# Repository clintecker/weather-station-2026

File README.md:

# Weather Station: bench prototype software

A home weather station, still on the bench. A sensor node (an STM32WL NUCLEO board) samples its sensors every 15 seconds. Once a minute it sends one observation, a summary of that minute, over encrypted LoRa to a second board on USB. A Python gateway (`ws0`) stores each reading in SQLite and acknowledges it over the radio. The gateway then serves the reading over a local HTTP API, a web dashboard and optional MQTT for Home Assistant.

This repository holds the firmware, the gateway, the tests, a fault-injection simulator, the bench hardware files and the dated evidence of each bench run.

Authority: the **Weather Station v0.2 product and technical requirements document (PRD/TRD), 8 October 2026**, sections 3, 9, 11 and the 24-hour delivery test (H01). H01 lives in section 12 of that document. The PRD/TRD itself is not in this repository.

Where things stand:

- The Python gateway (`ws0`) and the firmware for two NUCLEO-WL55JC1 boards (`firmware/stage0-node/`) live here.
- The boards run release `04fcc656938d` (TX) and `cc2766a38c61` (RX), protocol version 5. We built, flashed and tested that release on the bench, with the gateway of that release.
- Master is a step ahead. The firmware and the gateway on master speak protocol version 6 (power telemetry). Nobody cut them as a release yet, and they never met the boards ([`firmware/stage0-node/RELEASES.md`](firmware/stage0-node/RELEASES.md), "Next release").
- The project is the breadboarded development version (build steps 1 and 1b). We removed the later stages from the repository on 2026-11-02. Git history still has them.
- **The 24-hour delivery test (H01, [`docs/H01-checklist.md`](docs/H01-checklist.md)) did NOT RUN yet.**

Back at the bench after a break? Start with [`docs/CONTEXT-PACK.md`](docs/CONTEXT-PACK.md). Other entry points:

- Firmware: [`firmware/stage0-node/README.md`](firmware/stage0-node/README.md).
- Releases: [`firmware/stage0-node/RELEASES.md`](firmware/stage0-node/RELEASES.md).
- Move boards between gateways: [`docs/runbook-moving-boards.md`](docs/runbook-moving-boards.md).
- Tools: [`tools/README.md`](tools/README.md).
- The build sheets: [The bench build sheets](#the-bench-build-sheets).
- Every other document and package: [Where things are](#where-things-are).

The data path with the boards:

```mermaid
flowchart LR
  S["Sensor modules<br/>SHT45 and the bench station"] -->|"I2C, GPIO, ADC"| TX["TX board<br/>sensor node"]
  TX -->|"LoRa: encrypted observation"| RX["RX board<br/>USB bridge"]
  RX -->|"USB serial: hex line"| GW["Gateway<br/>ws0 serve"]
  GW --> DB[("SQLite")]
  GW -->|"ACK after the commit"| RX
  RX -->|"LoRa: encrypted ACK"| TX
  GW --> API["HTTP API<br/>127.0.0.1:8088"]
  GW -->|"optional"| MQ["MQTT broker"]
  MQ --> HA["Home Assistant"]
  API --> ST["tools/status.py"]
```

In the simulated demo, `ws0 demo` stands in for the boards. It sends encrypted frames to the same gateway code.

## The bench build sheets

The bench build sheets are illustrated PDFs that walk you through building the hardware, one step per page. They're the nicest thing in here, so have a look.

There are two sets:

- **TX stack, Sessions 1 to 5** (`hardware/tx-stack-r1/sheets/`). The printed base, the backplane and the four cards (B1 to B4) in their keyed 1x30 sockets.
- **Pods, Sessions P and Q** (`hardware/pods-r1/sheets/`). Session P builds the three pod boards and the port cable. Session Q covers the boxes, the shield and the install.

Why they are good:

- **Real geometry.** Every illustration comes from 3D models of the real parts (CadQuery and OpenCascade), with hidden lines removed and flat colour on each face. The renderer refuses a mirrored picture of a real object.
- **Exact parts.** The labels name the board, the face, the hole and the lead: "B4 POWER, TOP FACE", "X1 VIN+ (LEAD L2)", "backplane holes 13, 19, 27, 35". Nobody has to guess what "the card" means.
- **One step per page.** Each page opens with one big step number in a hazard-yellow box, then numbered panels with short captions.
- **Label chips that never collide.** Each label sits on a paper chip, and its leader stops at the chip edge. The build checks every page for chips that overlap, cross a panel edge or sit under another leader. One bad chip, and the build stops with `BUILD FAILED: label or hole-callout issues`.

The full tour, how the pipeline works and a reusable skill for other projects are in [`docs/build-sheets/README.md`](docs/build-sheets/README.md) and [`docs/build-sheets/skill/SKILL.md`](docs/build-sheets/skill/SKILL.md). The PDFs build into each `sheets/out/` folder and stay out of git.

## Run the simulated demo on your Mac

You don't need any boards for this. The demo fakes the radio side and runs the real gateway. Python 3.12 is the tested baseline. Open this folder in VS Code and run:

```sh
python3 -m venv .venv
source .venv/bin/activate
python -m pip install -r requirements.txt
python -m ws0 init
python -m ws0 demo
```

`init` creates a private `run-demo` directory with a fresh radio key, an API token and persistent nonce state. It refuses to overwrite an existing directory.

`demo` sends one simulated sample at once, then one every 60 seconds. It tests the path from encrypted frame to gateway to SQLite to encrypted ACK. The station name in records, the API and the MQTT topics is `simulation-01`. Its numeric radio station ID is 1. Ctrl-C stops the demo. Run `demo` again, and it resumes with a new observation epoch and the old queued history.

In a second terminal, from the same folder:

```sh
source .venv/bin/activate
python tools/status.py
```

This shows the live status and does not print your API token. The read-only API listens at `127.0.0.1:8088`. Every request needs the bearer token from `run-demo/gateway.json`. Routes:

- `GET /v1/status`
- `GET /v1/observations/latest`
- `GET /v1/observations?limit=100&offset=0`
- `GET /v1/observations?from=2026-10-09T00:00:00Z&to=2026-10-10T00:00:00Z&format=csv`

Times in records are Unix seconds UTC. `from` is inclusive and `to` is exclusive.

A sample with an unknown clock gets a reconstructed UTC time with an uncertainty. The gateway makes that time when a synchronized sample from the same boot epoch exists. Until then the effective time is null. SQLite keeps the sample, but `/v1/observations` never returns it.

A page holds at most 1,000 rows. [`docs/openapi.json`](docs/openapi.json) describes the interface, and the dashboard routes too.

The same port serves a live dashboard at `http://127.0.0.1:8088/`. It asks for the same token ([`docs/web-dashboard.md`](docs/web-dashboard.md)).

## Break things on purpose

While the demo runs, you can break things on purpose and watch how the gateway handles it. Run these commands in a second terminal. They act only on the simulator:

```sh
# Interrupt transport; leave demo running so it journals new observations.
touch run-demo/link-down
# After three missed reporting intervals, status becomes unavailable.
# Restore the path: live data is sent first, then at most five queued records/minute.
rm run-demo/link-down

# Make the next sensor samples explicitly invalid.
touch run-demo/sensor-fault
# Restore measurements.
rm run-demo/sensor-fault
```

Rules that the demo shows:

- The transmitter journal deletes a reading only after the gateway sends an authenticated reply. That reply is an ACK, or a NACK for a record that the gateway rejects for good. The firmware also drops a reading when the strike limit abandons it. A forged or unauthenticated reply never deletes a reading.
- The gateway makes the ACK only after the database commit.
- Old backfill and exact duplicate packets never refresh the age of a measurement.
- A newer sample whose sensors all failed marks the measurement unavailable. If only some sensors fail, only those fields go unavailable.
- A newer sample with an unknown clock stays unavailable until the gateway can reconstruct its time to within 10 s. The gateway uses a synchronized sample of the same boot epoch for that.
- The gateway quarantines a sample with a future clock when it arrives. The next correctly timed observation makes the measurement available again.

## Run with the boards

Both boards run the firmware in [`firmware/stage0-node/`](firmware/stage0-node/README.md). Find the port and the ST-LINK serial number of each board with `.venv/bin/python -m serial.tools.list_ports -v`.

**CAUTION:** Never provision a wiped TX board again with a key that it used before ([`docs/runbook-moving-boards.md`](docs/runbook-moving-boards.md)).

Start with an unprovisioned TX board. `WIPE ERASE-ALL-NODE-STATE` on its console erases it.

Use a new run directory (here `run-<name>`) each time you make a new key. `ws0 init` refuses a directory that exists.

```sh
.venv/bin/python -m ws0 init --hardware --station station-01 --station-id 1 --directory run-<name>
.venv/bin/python -m ws0 provision-node --directory run-<name> --serial /dev/cu.usbmodem<TX>
.venv/bin/python -m ws0 serve --directory run-<name> --serial-number <RX ST-LINK serial>
.venv/bin/python tools/status.py --directory run-<name>
```

`serve` writes receiver diagnostics to `run-<name>/receiver.log`. For unattended runs, use the launchd agent (`tools/deploy/macos/install.sh`) or the systemd unit (`tools/deploy/linux/ws0-gateway.service`). See [`tools/README.md`](tools/README.md). For Home Assistant, see [`docs/runbook-home-assistant.md`](docs/runbook-home-assistant.md).

The gateway runs on macOS and Linux. Windows is not supported.

## Run the simulation harness

The harness runs the demo in virtual time with faults injected. Each scenario covers a full virtual day.

```sh
# 15 deterministic scenarios, 24 virtual hours each; no hardware or broker required.
python -m ws0.harness --output my-simulation-results

# Inspect the generated report on macOS.
open my-simulation-results/report.html

# Edit a scenario JSON to change loss, delay, outages, clock faults or reboots.
python -m ws0.harness --scenario examples/scenarios/custom-outage.json --output custom-results

# Intentional failure control: this should exit with status 1 and report a missing row.
python -m ws0.harness --scenario examples/scenarios/short-baseline.json --negative-control --output negative-results
```

Each output directory must be new, so a repeated run cannot overwrite evidence. Fixed scenario seeds reproduce the raw frame and event traces.

The included `simulation-results/report.html` comes from an older campaign. It has 12 scenarios, recorded at commit 8aca123 with protocol version 1, before the `reboot-during-outage` scenario existed. In that campaign the gateway recovered all 17,280 observations. It found zero duplicate rows and zero nonce reuse. One noisy-link seed delivered 98.82 % on time, below the 99 % target.

A scenario PASS means that its declared recovery and integrity contract passed. It is not a pass of the 24-hour delivery test. [`docs/simulation-harness.md`](docs/simulation-harness.md) gives the exact model and its limits.

## Home Assistant and MQTT

The weather, on your home dashboard. The gateway can publish to MQTT, with Home Assistant discovery for these items:

- Every observation field that the station sends: temperature, humidity and the values of the other bench modules. From protocol version 6, the power rails come too, as diagnostic entities.
- The power keys of the node health report.
- One diagnostic sensor per module type.

The details are in [`docs/runbook-home-assistant.md`](docs/runbook-home-assistant.md), "Power entities". MQTT is off by default, so the demo runs without a broker.

To enable MQTT:

1. Stop the service.
2. Edit `run-demo/gateway.json`. Set `mqtt.enabled` to true and set the broker hostname and port.
3. If the broker needs a user name, add `mqtt.username`. For a TLS broker, set `mqtt.tls`.
4. Put the password in the environment variable `WS_MQTT_PASSWORD`, or in the file `<run dir>/mqtt-password`. The source code does not store it.
5. Start the service again. The gateway reads the configuration only at start.

You must configure the broker in Home Assistant first. This repository changed no Home Assistant instance and no broker. The simulated device appears as **simulation-01**.

Its sensors are available only while the gateway health and the measurement freshness are both online:

- The gateway uses an MQTT last will to report its disconnection.
- A measurement goes offline when it is older than the station's live interval plus 120 seconds, by the energy state it carries: 180 s in SURPLUS and NORMAL, 420 s in CONSERVE, 3,720 s in CRITICAL (`current_max_age` in `gateway.py`). A health report goes offline after 1,900 s, or 3,720 s in CRITICAL.
- The gateway publishes discovery again when the broker reconnects.

The temperature and humidity sensors meet the weather-data integration requirement of the bench prototype. The gateway does not make a forecast or composite weather entity, because no data supports one. (No crystal ball yet.)

A test against a local Mosquitto broker verified discovery, last will and reconnect (`evidence/mqtt-local-broker-2026-10-13/`). Against Clint's Home Assistant, the HA-user broker login and the device's discovery passed (`evidence/ha-broker-2026-10-22/`). Nobody tested TLS. Use a separate station ID and key for hardware. Never use the demo state to provision real boards.

## What works today

- AES-128-CCM authenticated observation and ACK frames.
- Durable allocation of the host nonce, binding of the endpoint and key, and a separate observation identity.
- SQLite storage, immutable deduplication and collision rejection.
- A persistent simulated transmitter queue, restart handling and bounded backfill.
- An authenticated loopback HTTP API for status and history, with CSV export.
- Optional MQTT snapshots, availability and Home Assistant discovery.
- USB serial input from the RX board (`ws0 serve`), with the ACK/NACK return path.
- Portable C code for the SHT45: acquisition, CRC check and conversion.
- The TX reads its sensors as DATAVANE5K local modules, with the module protocol WSMP ([`docs/module-protocol.md`](docs/module-protocol.md)). The source has eight modules: outside air, pressure, UVA, enclosure, battery, power rails, wind and rain (`firmware/stage0-node/App/mod_*.c`, `App/wsmp_host.c`). The boards' release `04fcc656938d` has seven, with one power module.
- Power telemetry, protocol version 6 (in the source, no version 6 release yet). Design: [`docs/superpowers/specs/2026-10-29-power-telemetry-design.md`](docs/superpowers/specs/2026-10-29-power-telemetry-design.md).
  - The node reads power phase A on the 1S3P pack. From the bq24074 charger it reads ISET, input voltage, CHG and PGOOD. It also reads the battery INA228 and the MAX17048 gauge.
  - Every minute it sends the battery voltage and signed current, the load voltage and the charger input voltage.
  - Every 15 minutes it sends a 64-byte health report. The report holds these values:
    - gauge SOC and rate, charger status, die temperature and MCU supply
    - reset cause, boot and crash counts and the last crash PC
    - radio TX timeouts and I2C recoveries
  - The gateway stores these values and shows them through the API, the dashboard and MQTT.
- TX and RX firmware (`firmware/stage0-node/`):
  - A flash journal of at least 609 records, about 10.15 hours, of the version 6 node field set (77 bytes in 96-byte slots).
  - The version 5 release `04fcc656938d` held 1,725 records, 28.75 hours.
  - A build whose field set exceeds 80 bytes does not compile.
  - Durable counters and epochs, a watchdog, and provisioning over USB.
- Python and C tests that target failures, and recorded validation output.

## Current state and open work

Here is the honest scoreboard. The releases are in [`firmware/stage0-node/RELEASES.md`](firmware/stage0-node/RELEASES.md). The TX runs release `04fcc656938d` (flashed 2026-10-19). The RX runs release `cc2766a38c61`, because the RX code did not change.

No gateway runs right now. The last gateway session served run directory `run-d7` and stopped on 2026-10-19 at 21:58 UTC, when the boards went home. That run directory and its key are no longer in this checkout. The next bench run starts a new run directory and key (`ws0 init`, `WIPE` on the TX, `provision-node`).

The track record so far:

- On the earlier release `a07f498273f7`, a 9-hour bench soak delivered 549 of 549 minutes on time (`evidence/soak-a07f498-2026-10-13/`).
- Two lab rehearsals with the H01 scoring rules followed. The first got 1,440 of 1,440 intervals on time on release `bc5e6ede429c` (`evidence/h01-rehearsal-2026-10-14/`).
- The second got 960 of 960 over 16 hours on release `7eb79f64f2bd` and ended early (`evidence/h01-rehearsal-2026-10-15/`).
- Neither rehearsal is H01. Both ran with bench radio settings, away from the intended placement.

The radio settings are bench values (`firmware/stage0-node/App/radio_cfg.h`): 915.0 MHz, 500 kHz bandwidth, spreading factor 7, coding rate 4/5, 0 dBm.

Open before the 24-hour delivery test (its preconditions: [`docs/H01-checklist.md`](docs/H01-checklist.md)):

- The step 1 build (breadboard v2) exits on every criterion, mode B for 1 hour included. The breadboard build, where H01 runs, has a `valid` preflight block that includes the 1 A spans (build-progression record section 3).
- The USB acceptance test H8(d) passes on the H01 topology (the RX alone on a direct Mac port, 7.1 Q5).
- The running gateway carries the ws0 silent-port reopen from `ws0/link.py`, loaded by a gateway agent restart (record H8(f)).
- Home Assistant entities update live, with the gateway logged in on the rotated password. (Login and discovery passed a check on 2026-10-22.)
- The link budget at the real placement, the antennas and the current measurements.
- The 24-hour run with its restart and outage matrix.
- Clint's open decision D2: does H01 run on a protocol version 6 (power telemetry) release? The recommendation is yes. The H01 preconditions as written (`meter_link=ok` from the M7 probe, the power phase A exit criteria) need a version 6 build. A "no" needs a version 5 backport of the M7 probe and the power reading, and no plan carries one ([`docs/H01-checklist.md`](docs/H01-checklist.md)).

Power phase A exit criteria 1 and 2 (node firmware and gateway) gate H01 (build-progression record, section 3, step 1 note). They are not step 1 exit criteria, so H01 precondition 1 (step 1 exit) does not include them. The exit criteria are in the [power telemetry design](docs/superpowers/specs/2026-10-29-power-telemetry-design.md), section 2. Open for power phase A:

- Measure the phase A constants (R_ISET, the divider ratio, the TMR strap). Check the INA228 shunt against a series reference. Cut a version 6 release.
- The node-against-benchlink acceptance drill with the cell through the shunt.
- A 1 A charge with the shunt in the battery path that ends in a normal termination.
- Decision D1 (the 1S3P pack, about 24.4 Wh, against the PRD's energy reserve) is settled for now: Clint confirmed a 25 mW planning load on 2026-11-22, which sets CONSERVE at 30 / 35 % SOC and 3.60 / 3.70 V and CRITICAL at 8 / 13 % and 3.45 / 3.55 V ([`docs/radio-energy-policy.md`](docs/radio-energy-policy.md) section 3). H02 replaces the planning load. The energy state is live in the TX stack build (power profile 3); the bench profiles 1 and 2 stay NORMAL.

Open bench checks of the DATAVANE5K bench station (GitHub issues #2, #3 and #4, label `needs-bench`):

- #2: the INA228 charge and energy accumulators.
- #3: the wind vane ADC calibration.
- #4: the anemometer input filter on PB5.

The bench station wiring is in [`docs/hardware/bench-station-wiring.md`](docs/hardware/bench-station-wiring.md). The breadboard map is in [`hardware/bench-breadboard-r0/`](hardware/bench-breadboard-r0/README.md).

Simulation cannot pass the 24-hour delivery test. The 30-day on-device storage requirement belongs to the later qualification H11. The ordered next steps are in [`docs/CONTEXT-PACK.md`](docs/CONTEXT-PACK.md) §6.

## Tests

The safety net. Fetch the vendor code once, then run the suite:

```sh
sh tools/fetch-vendor.sh   # pinned STM32CubeWL + Mbed TLS; without it the tests that need Mbed TLS skip
WS0_UNSAFE_FAST_FSYNC=1 python -m unittest discover -s tests -v
```

On 2026-10-19 at commit 09e6cea, the suite had 595 tests and all gates passed (commit e379cff). The count grew since then: [`tests/README.md`](tests/README.md) records 1,304 tests collected on 2026-10-30.

Some tests need extra tools:

- One SNTP test needs the network and skips without it.
- The C tests need `cc` (Apple Command Line Tools on macOS).
- The dashboard script tests need `node`.
- The KiCad tests in `test_breadboard.py` (the Board and Outputs classes) need KiCad 10 and `tools/fetch-router.sh`. The breadboard-map model and sheet tests need neither.
- Other tests skip when `make`, the ARM toolchain, CadQuery/numpy, Pillow, the shield 3MF, the BOB-14021 STEP or IPv6 is missing.

Each test skips and says why when its tool is missing. [`tests/README.md`](tests/README.md) lists what most test files cover (47 of 66) and the main environment variables. The 1,440-record test uses accelerated virtual timestamps, not 24 hours of real time. `evidence/validation.txt` is a historical record: 28 tests at commit 8aca123.

`tools/gates.sh` runs the CI gates locally on macOS or Linux: ruff, code shape, cppcheck, two clean firmware builds, analysis, the tests and the fuzzers.

**CAUTION:** `WS0_UNSAFE_FAST_FSYNC=1` is **only for tests**. Never set it for a gateway that acknowledges real data. It sets SQLite `synchronous=OFF` and turns off `fullfsync`. As a result, a commit might not survive a power loss or an OS crash, and the database can become corrupt.

## Keep the keys secret

Keys are the crown jewels here, so treat each run directory like a wallet. Keep the whole run directory private. Obey these rules:

- Never copy a run directory to two hosts that run at the same time.
- Never restore an older nonce state and keep its key.
- If the nonce state is lost or rolled back, retire that key. Provision a new configuration for both ends.
- Never use a known key with a reset counter.
- Do not commit keys, tokens or run databases.

The host counters persist in SQLite. On the TX board, the counters and boot epochs persist in flash (`firmware/stage0-node/App/node_store.c`). A wiped node needs a new key ([`firmware/stage0-node/README.md`](firmware/stage0-node/README.md), "Re-keying rule"). The downloadable archive contains no working secrets.

## What comes next

See [`docs/CONTEXT-PACK.md`](docs/CONTEXT-PACK.md) §6 for the ordered list. Power phase A (the bq24074 charger and its monitors on the 1S3P pack, read by the node) runs now, on the step 1 build, before H01. H01 runs on the breadboard build only after step 1 exits (build-progression record section 3). Step 1b adds the load, solar and USB-C rails on the same breadboard build.

This repository adds no charger or pack control, no RJ45/Modbus (off-board wired-module bus) abstraction, no heater and no shared charging. The node measures the power system and never controls it. Look, don't touch.

Power phase A measures the battery (cell voltage and signed current), the load voltage and the charger input voltage. It cannot tell if that input comes from solar or USB-C. The final goal is the voltage and current of four rails: battery, solar input, USB-C input and load. Phase B (step 1b) adds one INA228 per rail ([`docs/hardware/power-metering.md`](docs/hardware/power-metering.md)). USB-C is for bench work and occasional backup charging only, never connected together with solar.

## Where things are

| Path | What |
|---|---|
| [`docs/CONTEXT-PACK.md`](docs/CONTEXT-PACK.md) | Where to start: state, setup and next steps. §8 maps the main documents |
| [`docs/build-sheets/`](docs/build-sheets/README.md) | The bench build sheets: the showcase, how the pipeline works, and a reusable skill (`skill/SKILL.md`) |
| [`hardware/tx-stack-r1/sheets/`](hardware/tx-stack-r1/sheets/) | Sources of the TX stack build sheets, Sessions 1 to 5 |
| [`hardware/pods-r1/sheets/`](hardware/pods-r1/sheets/) | Sources of the pod build sheets, Sessions P and Q |
| [`docs/superpowers/specs/2026-10-29-power-telemetry-design.md`](docs/superpowers/specs/2026-10-29-power-telemetry-design.md) | Power telemetry design: phases, the per-phase fill table, protocol version 6, the 64-byte health report, node firmware, gateway |
| [`docs/superpowers/specs/2026-10-29-build-progression-decisions.md`](docs/superpowers/specs/2026-10-29-build-progression-decisions.md) | The build-progression decision record: build steps 1 and 1b on the breadboard, the NUCLEO pin contract, the step 1 build and shopping, the cascade list. Clint's survey answers (2026-10-30) are in section 7.1 |
| [`docs/superpowers/plans/2026-10-29-power-telemetry.md`](docs/superpowers/plans/2026-10-29-power-telemetry.md) | Power telemetry implementation plan |
| [`docs/superpowers/plans/2026-10-29-power-telemetry-issues.md`](docs/superpowers/plans/2026-10-29-power-telemetry-issues.md) | Power telemetry issue catalog: each issue's layer, severity, batch and state |
| [`docs/superpowers/plans/2026-10-30-build-progression-issues.md`](docs/superpowers/plans/2026-10-30-build-progression-issues.md) | Build progression issue catalog: each issue from the decision record and Clint's 2026-10-30 answers, by area, severity, batch and state |
| [`docs/hardware/power-metering.md`](docs/hardware/power-metering.md) | Power metering: rails, monitors, addresses, shunts and sense points in each phase |
| [`docs/H01-checklist.md`](docs/H01-checklist.md) | The 24-hour delivery test |
| [`docs/firmware-current-design.md`](docs/firmware-current-design.md) | The design sections the firmware implements: the mux profile, module identity, the module record, the flash layout |
| [`docs/protocol.md`](docs/protocol.md), [`docs/protocol-design.md`](docs/protocol-design.md), [`docs/protocol-stack.md`](docs/protocol-stack.md) | The radio protocol: specification, design rationale, layered explanation |
| [`docs/module-protocol.md`](docs/module-protocol.md) | DATAVANE5K, the module protocol WSMP |
| [`docs/hardware/bench-station-wiring.md`](docs/hardware/bench-station-wiring.md) | How the bench station sensors connect to the TX board |
| [`docs/hardware/nucleo-wl55jc-bringup.md`](docs/hardware/nucleo-wl55jc-bringup.md) | Board bring-up log |
| [`docs/failure-modes.md`](docs/failure-modes.md) | Failure modes, loss budget, recovery runbook |
| [`docs/firmware-budget.md`](docs/firmware-budget.md), [`docs/firmware-event-model.md`](docs/firmware-event-model.md), [`docs/power-of-ten.md`](docs/power-of-ten.md) | Firmware budgets, run-time model, coding rules |
| [`docs/runbook-moving-boards.md`](docs/runbook-moving-boards.md), [`docs/runbook-home-assistant.md`](docs/runbook-home-assistant.md) | Runbooks |
| [`docs/superpowers/`](docs/superpowers/) | Design specifications and implementation plans |
| [`ws0/`](ws0/README.md), [`gateway.py`](gateway.py) | The gateway package and its SQLite store |
| `*.lit.md` ([`gateway.lit.md`](gateway.lit.md), [`ws0/protocol.lit.md`](ws0/protocol.lit.md), eleven under `firmware/`, 13 in all) | Literate sources. Each is the source of the committed `.c` or `.py` file it generates (`tools/tangle.py`). Edit the document, not the generated file |
| [`firmware/`](firmware/README.md) | Board firmware, fuzz targets and the range-test tool |
| [`tools/`](tools/README.md) | Scripts, CI gates and service files |
| [`tests/`](tests/README.md) | Python and C tests |
| [`examples/scenarios/`](examples/scenarios/) | Two scenario files for `ws0.harness --scenario`: `custom-outage.json` (240 minutes, an outage and a reboot. Edit it) and `short-baseline.json` (10 minutes, the negative-control fixture) |
| [`simulation-results/`](simulation-results/) | The committed output of an older harness campaign: 12 scenarios at commit 8aca123 ([Run the simulation harness](#run-the-simulation-harness)) |
| [`.github/workflows/ci.yml`](.github/workflows/ci.yml) | CI ([`tools/README.md`](tools/README.md#ci)) |
| `requirements.txt`, `requirements-dev.txt`, `ruff.toml` | Pinned gateway dependencies. Pinned lint, code-shape, Cppcheck and Pillow for development and CI. The ruff bug rules |
| `VALIDATION.txt` | A four-line pointer: the historical 28-test record (`evidence/validation.txt`, commit 8aca123) and the command for the current suite (595 tests on 2026-10-19). See [Tests](#tests) |
| `vendor/` (git-ignored) | Pinned third-party checkouts: STM32CubeWL with Mbed TLS (`tools/fetch-vendor.sh`), KiCadRoutingTools and its Python environment `krt-venv` (`tools/fetch-router.sh`). Never edit. Fetch again |
| `run-*/` (git-ignored) | Gateway run directories. Each holds one radio key and its data: `gateway.json` (key, API token, settings), `observations.sqlite3`, the nonce state `gateway-nonces.sqlite3`, logs such as `receiver.log`, and an optional `mqtt-password`. One directory per key. `run-demo` is the simulator's. No run directory is current: on 2026-11-18 every earlier run directory (`run-hw`, `run-office`, the `run-d5`/`run-d6` archives, `run-d7`) was deleted. The next bench run starts with a new run directory and a new key (`ws0 init`, `WIPE` on the TX, `provision-node`). Keep them private. Never commit them |
| [`hardware/bench-breadboard-r0/`](hardware/bench-breadboard-r0/README.md) | Breadboard map of the bench station: build sheet, renders, KiCad model |
| [`hardware/base-plate/`](hardware/base-plate/spec-r2.md) | The printed bench base plate: its spec |
| [`evidence/`](evidence/README.md) | Every bench run, dated |

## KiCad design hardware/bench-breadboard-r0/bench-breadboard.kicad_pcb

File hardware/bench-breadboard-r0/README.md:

# Bench breadboard map (r0)

This is the bench station's sensor suite on three 830-point breadboards, wired to the TX board
(NUCLEO-WL55JC1, board A). It's a KiCad 10 model of the breadboard build, the first step of
[`docs/hardware/bench-station-wiring.md`](../../docs/hardware/bench-station-wiring.md). That guide is the
electrical source of truth for the signals.

The model describes the **step 1 v2 target** of the build-progression record,
[`docs/superpowers/specs/2026-10-29-build-progression-decisions.md`](../../docs/superpowers/specs/2026-10-29-build-progression-decisions.md).
That target is changes A and B and the second QT cable (sections 4.4-4.6), and it's revision `bench-bb-r0.3` in `source/wiring.toml`. Here's what it looks like:

- Every battery, charge and load current runs on leads between lever connectors, JST PH sockets and
  screw terminals, never through a breadboard contact (record P1). The one exception is the regulator's
  mode-B supply chain, which P1 allows and the model tags `P1 regulator`.
- The breadboards carry only signals and sense taps, plus the regulator's supply chain in mode B, which
  record P1 allows.
- The NUCLEO's station signals land on its Arduino headers. The bench OLED on board C uses the morpho
  headers: its signals on CN10, its supply from CN7.16 and CN10.20.
- The mode-B supply enters at CN6.4.
- The hub's sensors and the power monitors are on two QT cables, both on the unswitched 3V3.

Change C, the PA9 sensor switch, isn't part of the breadboard build (record 4.6 dated note, 2026-11-02).
The bench has no sensor power switch. The power design is
[`docs/superpowers/specs/2026-10-29-power-telemetry-design.md`](../../docs/superpowers/specs/2026-10-29-power-telemetry-design.md)
sections 11.1 and 11.2, as the record amends them.

**To build, open [`build-sheet.md`](build-sheet.md)** and the renders. That's the current revision,
`bench-bb-r0.3`. You build the bench one change at a time from the r0 bench (record 4.4-4.6):

- change A from [`revisions/bench-bb-r0.1/build-sheet.md`](revisions/bench-bb-r0.1/build-sheet.md)
- change B from [`revisions/bench-bb-r0.2/build-sheet.md`](revisions/bench-bb-r0.2/build-sheet.md)
- the second QT cable (QTM) from `build-sheet.md`

Each sheet has a "Changes from the previous revision" section. It says what comes out and what goes in,
compared with the sheet before. Before you place a wire, tick the wiring guide's section 6 checklist
against UM2592. Then work through the build sheet in this order: the bench checks before you connect
power, the pre-run checklist (C1-C23), and power checks 1-10 in order.

| Render | Shows |
|---|---|
| [`renders/board-a.png`](renders/board-a.png) | board A, signals: both RJ11 breakouts with the meter pull-ups and filters at the jack end, the STEMMA QT cable to the hub (QT) and the one to the power monitors (QTM), both unswitched |
| [`renders/board-b.png`](renders/board-b.png) | board B: the bq24074 charger's header with its ISET network (R_ISER, C_ISET, R_IPD) and the 20 kΩ/10 kΩ input divider (R4-R6), the INA228, the fuel gauge, the regulator, the BATTERY POWER shunt. Off the breadboard: the pack, the 100 Ω load, the NTC, the wall adapter and the four WAGO joints with their leads |
| [`renders/overview.png`](renders/overview.png) | the boards and the jumpers to the NUCLEO headers (not to scale) |
| [`renders/3d-top.png`](renders/3d-top.png), [`renders/3d-angle.png`](renders/3d-angle.png) | KiCad 10's 3D view |
| [`renders/schematic.pdf`](renders/schematic.pdf) | the wiring schematic, drawn as circuits with KiCad's own symbols. The meter's reed switches and vane resistors sit across the RJ11 breakout pins their cables reach |

The build sheet prints the `wiring.toml` git blob that the renders came from. If that differs from the
model's blob, the sheet says the renders lag the model. In that case, go by the sheet.

The third breadboard stays spare (for the W25Q128 flash later).

```mermaid
flowchart LR
  T["source/wiring.toml"] --> J["jumper plan"]
  J --> C["checks: wiring guide both ways, firmware pins, connectivity proof, D3 checks"]
  C --> S1["make.py sheet: build sheets, connections.json"]
  C --> K["make.py all: KiCad 10 board"] --> R["KiCadRoutingTools: jumpers"] --> D["DRC"]
  C --> S["schematic"] --> E["ERC"]
  D --> O["renders"]
```

So `wiring.toml` feeds the jumper plan. Then the checks run in this order: the wiring guide both ways,
the firmware pins, the connectivity proof, then the D3 checks. Every check has to pass before any file
gets written.

## What each check proves

| Check | Proves |
|---|---|
| `check_guide` | each NUCLEO pin the map uses is in the wiring guide's section 2 table, on a header the guide lists |
| `check_guide_reverse` | the other way round (record D3 check 7): each guide row that names a station pin has a model net with that `mcu` pin, unless the row says "protoboard only" or "carrier only" |
| `check_firmware` | each pin matches the constants in the bench link's `App/benchlink.c`, in i2cscan's `App/i2cscan.c`, and, for the node, in the generated header `firmware/board/nucleo-wl55jc/gen/board_pins.h` (BOARD_CUPS/VANE/ISET/VIN/RAIN/PGOOD/CHG_PIN, BOARD_I2C_SDA/SCL_PIN and the five BOARD_OLED_*_PIN). `tools/boardgen.py` generates that header from `board.toml`. The OLED's five SPI and control pins (BOARD_OLED_CS, SCK, MOSI, RST and DC) come from that header too. `oled_spi1.h`, which i2cscan and the node's bench build share, takes its pins from it, and `check_firmware` doesn't read `oled_spi1.h`. PA9 (POWER_PIN) isn't checked, because the model has no SENS_EN (change C isn't built). An ADC input (vane, ISET, VIN_SENSE) uses its pin's ADC1 channel (D3 check 8) |
| `prove` | the strips, the jumpers, the leads, the joints, the ties inside parts and the NUCLEO's own ties join every net, with no short and no stray pin |
| `checks.check_force_off_breadboard` | D3 check 1: no force lead or force-net member in a breadboard hole, except the P1 regulator chain, tagged member by member |
| `checks.check_sense_landings` | D3 check 2: no sense lead shares a clamp position with a force lead, and each lands on its declared joint |
| `checks.check_single_tie` | D3 check 3: one conductor (L_TIE) joins the power and logic grounds, and no logic-supply current flows on the board-B ground rail |
| `checks.check_gauge_upstream` | D3 check 4: the gauge's sense lead is on CELL_POS, upstream of the shunt |
| `checks.check_shunt_only` | D3 check 5: nothing but the shunt joins INA VIN+ and VIN- |
| `checks.check_test_point_strips` | D3 check 6: each breakout test-point pin is alone in its strip |
| `checks.check_meter_at_jack` | record M7's placement rule: each meter pull-up and filter (R1 and C_CUPS, R2 and C_RAIN, R3) has its line-side lead in its BOB-14021 pin's own strip. So no jumper sits between the jack pin and its pull-up, out of the counter link probe's sight |
| `checks.check_iset` | D3 check 8's ISET constants (record step 1 exit 7): `POWER_R_ISET_OHM` in `power_config.h` equals the charger's `iset_ohms` (R9, 1 kOhm), `POWER_ISET_GAIN_PPM` equals R_IPD / (R_ISER + R_IPD) in ppm (990099), and `tools/benchlink_log.py`'s `R_ISET_OHM` and `ISET_GAIN` defaults carry the same two values |
| `checks.check_divider` | D3 check 9: the firmware's divider ratio equals the model's R4-R6 |
| `checks.check_lead_lengths`, `checks.check_lead_geometry` | record H7's lead lengths, and each lead at least as long as its drawn span |
| KiCad DRC | every jumper runs between its two planned holes, clear of every other hole: 0 errors, 0 unconnected |
| KiCad ERC | the schematic has 0 errors, and a test checks that its nets equal the model's |

Every check except DRC and ERC runs without KiCad, in both regeneration tiers.

## Regenerate

There are two tiers (record D4). Both stamp their output with the `wiring.toml` git blob hash.

```sh
.venv/bin/python hardware/bench-breadboard-r0/source/make.py sheet    # no KiCad: every model commit
tools/fetch-router.sh                                                  # once: KiCadRoutingTools v0.23.1, pinned (macOS arm64 only)
tools/fetch-cad.sh                                                     # once: the makers' 3D models of board B's parts, pinned
.venv/bin/python hardware/bench-breadboard-r0/source/make.py all      # KiCad: step exits and net changes
.venv/bin/python -m unittest tests.test_breadboard tests.test_breadboard_checks
```

- **`make.py sheet`** loads the model, plans the jumpers and runs the checks (the table above). Then it
  writes `build-sheet.md` and `connections.json`. It also writes the same two files for each frozen
  earlier revision into `revisions/<revision>/` (below). Run it on every commit that changes
  `wiring.toml`. Every bench rewire is one commit with the model and the regenerated sheet.
- **`make.py all`** does the same, then draws the KiCad board, routes it and runs DRC. It also draws the
  schematic (with ERC), the 3D view and the renders. Run it at every step exit and whenever nets change.
  `layout.json` records the model hash it drew (`model_hash`). The build sheet prints it beside the
  model's own hash, so you can see when a render lags.
- **`connections.json`** sits beside each sheet (generated). It lists every jumper, link and lead by net and
  ends, with its stable id where it has one. It also keeps the baseline the sheet compared against.

  The sheet's **"Changes from the previous revision"** section lists what to remove, then what to add. It
  names each wire by net and endpoints, never by W-number. Each regeneration reassigns W-numbers in build order, so any model change can renumber them. The same model always gives the same numbers.
- **Revisions and tags.** There are three revisions:
  - `bench-bb-r0.1` (change A)
  - `bench-bb-r0.2` (change B, the meter pin remap)
  - `bench-bb-r0.3` (the second QT cable). *2026-11-02:* we redefined it in place before anyone built
    it, without change C, the PA9 sensor switch, which isn't part of the breadboard build.

  `source/wiring.toml` is the current one (r0.3). The earlier ones are **frozen models**,
  `source/revisions/bench-bb-r0.1.toml` and `bench-bb-r0.2.toml` (`make.py`'s `HISTORY`). Each one is the
  whole bench as its change leaves it. Their regenerated sheets live in `revisions/<revision>/` (record
  6.1 dated note). Each sheet's baseline is the revision before it, regenerated from its model. For r0.1
  that's `source/baseline-2026-10-29.json`, the r0 sheet the bench was built from (parsed once from its
  committed jumper table).

  A frozen model gets the connectivity proof and the D3 checks. The wiring guide and the firmware
  describe the current revision, so only `wiring.toml` gets checked against them. A frozen model has no
  renders. `tools/preflight.py` checks a preflight block against the frozen model and sheet that its
  `revision` names. If a model change applies to the bench at every revision (say, a part moved before
  anything is built), it goes into all three models.

  To start a new revision, copy `wiring.toml` to `source/revisions/<its revision>.toml` and add it to
  `HISTORY`. Then bump `wiring.toml`'s `revision`. Clint makes the matching git tags. Step 1b's INA228
  rails aren't in the model yet.

KiCad 10 comes from `KICAD_APP` (default: the 10.0.6 disk image on the bench Mac,
`tools/kicad_env.py`). The router's prebuilt binary is for macOS arm64, so `tools/fetch-router.sh`
skips on other hosts. Without KiCad or the router, `make.py all` stops and says so. The KiCad tests
skip and say what's missing. `make.py sheet` and the model tests still run.

Without `vendor/cad` (`tools/fetch-cad.sh`), the 3D view draws plain boxes for the breakouts and the pack
instead of the makers' models. The committed renders use the makers' models.
Two `make.py all` builds give a byte-identical routed board (`bench-breadboard.kicad_pcb`), and
`test_generation_is_deterministic` tests that. `test_sheet_runs_without_kicad` compares the build sheet
across two runs.

## How the model works

- A jumper is one wire between two free holes. The model picks the holes, never one a part uses, and
  puts one wire in each hole. In KiCad each jumper is its own two-pad net (`W1`, `W2`, ...). Every other
  hole is a pad with no net, so the router only finds the path. The model proves the wiring itself.

  A `[[link]]` is a jumper the wiring guide requires, with a stable id (`LK_REG_SHUNT`, `LK_3V3_CN6_4`,
  `LK_QT_GND_CN6_6`). The build sheet names it beside its W-number.
- Jumpers show up as copper traces, because KiCad has no flying wires. The two copper layers are only
  drawing layers, since the wires cross freely.
- The 3D view is `bench-breadboard-3d.kicad_pcb`, a copy of the routed board with 3D models only. It
  uses KiCad's own models where its library has one: the resistors, the capacitors, the pin headers and
  the NUCLEO's headers (pin sockets for CN5, CN6 and CN8, pin headers for the morpho rows). KiCad has no
  breadboard, so `source/models.py` writes one: an 830-point body 8.5 mm tall with its holes and rail
  stripes.
- Each jumper in 3D is a wire 2 to 3.2 mm above the breadboard, staggered in 0.4 mm steps. It follows
  the layout's path where there is one (between boards and to the NUCLEO), otherwise its routed copper.
  It has legs into its two holes.
- The committed 3D view uses the makers' own models (`vendor/cad`) for the charger, INA228, gauge,
  regulator and pack. The RJ11 breakouts with their jacks, the OLED, the NTC, the adapter and the WAGO
  joints are boxes at their real outlines. Without `vendor/cad`, the breakouts and the pack fall back to
  boxes.
- Each breakout's header sits on row a, and its board overhangs outward, over the rails and off the
  edge. No jumper or part uses a hole under a breakout (`test_no_jumper_lands_under_a_breakout`).
- A **joint** (`[[joint]]`) is a WAGO 222 lever connector off the breadboard, beside board B. It's one
  node, with its positions numbered from 1 (CELL+, BATT, OUT and STAR, record P3-P6). The build sheet
  lists what lands in each position (section 4).
- A **lead** (`[[lead]]`) is a wire off the breadboard with a role (force, sense, signal or supply), a
  gauge, a kind (pigtail, solid, cable or dupont) and a length (record D2). Outside the P1 regulator
  chain, no force lead ends in a breadboard hole or on a NUCLEO pin (`checks.check_force_off_breadboard`).
  A force lead ends in a lever clamp, a screw terminal, a JST socket, the charger's USB-C receptacle or an
  off-board part's own terminal, or it's insulated. Only sense leads, the OLED's supply pair and the P1
  regulator chain end in a breadboard hole or on a NUCLEO pin.

  The proof joins a lead's two ends. The build sheet lists leads separately (section 3). The schematic draws each one as a heavy line with a
  note, and the renders and the 3D view draw it straight between its ends.
- An off-board part (the pack PACK, the 100 Ω load RLOAD, the thermistor NTC, the wall adapter ADAPTER)
  sits beside board B at its `place_mm`. It has terminals only, so leads join it and no strip does.
- The charger's BATT and SYSOUT sockets and the INA228's X1 are terminals too. Each one connects inside
  the part to the header pins it shares, and those pins stay zero-current test points (record P2). The
  gauge's BAT1 socket is a terminal as well, but its header carries no battery pin, so it has no
  internal tie.
- A part pin left open (a breakout pin in no net) owns its strip.
- The drawings show mode A, the daily mode: the BATTERY POWER shunt is open and the 100 Ω load is
  fitted. The build sheet gives the steps to mode B and back, with ground untouched (section 7).

## Decisions

- **PA9 is unconnected** on the breadboard build (*2026-11-02*, record 4.6 dated note), because change C,
  the PA9 sensor load switch, isn't built. The firmware may still drive PA9, and that's harmless here.
  We redefined `bench-bb-r0.3` in place (nobody had built it yet). r0.1 and r0.2 stay frozen. The second
  cable QTM still takes the battery INA228 (0x40) and the MAX17048 (0x36) from the same unswitched 3V3 as
  the hub's cable QT. That's redundant now, but harmless, and QTM carries the step 1b INA228 daisy chain
  (record 4.6).
- **PGOOD and CHG** jumper from the charger's header on board B to the NUCLEO's Arduino header:
  CHG to CN9.7 (D6, PB10), PGOOD to CN9.6 (D5, PB8). Their morpho aliases CN10.25 and CN10.27 stay
  empty (record N1, N3).
- **The regulator output feeds the NUCLEO's 3V3 at CN6.4.** It goes through the SHUNT, L_REG_3V3 and the
  QT.V+ strip (A:c41), where L_REG_3V3 and LK_3V3_CN6_4 both land. That strip is on the board-A 3V3 net,
  the same net as CN7.16. The chain never goes through the A:L+ rail: it has no planner jumper and no
  rail contact. There's no link to CN7.16. Each member of this P1 regulator chain (L_REG_VIN, L_TIE,
  L_NUC_RET, LK_REG_SHUNT, SHUNT, L_REG_3V3, LK_3V3_CN6_4) carries `exception = "P1 regulator"` in
  `wiring.toml`.
- **The bench OLED** takes its supply on its own pair straight from the NUCLEO: VCC from CN7.16, GND to
  CN10.20 (L_OLED_VCC, L_OLED_GND, record N3). It never goes through a breadboard rail. You unplug its
  VCC lead in mode B.
- **RJ11** is the weather meter's own cable connector (SparkFun SEN-15901). The BOB-14021 breakouts are
  its sockets. You solder their PRT-00132 jack and header pins on as module preparation (record H5,
  7.1 Q6), then check each conductor (build sheet, bench checks). The v1 sensor ports are RJ11 per the
  ports spec, and v1 has no RJ45 (H6).
- **The meter's reed switches and vane resistors** are inside the SEN-15901. The meter circuits on
  board A add only R1-R3, C_CUPS and C_RAIN, at the jack end. Each one has its line-side lead in its
  BOB-14021 pin's own strip (record M7, `checks.check_meter_at_jack`).
- **ISET and the input divider** go to the ARDUINO header CN8 (solid 22 AWG):
  - ISET goes through R_ISER (10 kΩ 1 % at the charger) to the PB1 node, on CN8.1 (A0, ADC1_IN5). C_ISET
    (100 nF) and R_IPD (1 MΩ) go from that node to logic ground (record M2).
  - VBUS goes through R4 + R5 (20 kΩ) over R6 (10 kΩ) to PA10 (CN8.3, A2, ADC1_IN6).
  - You measure each divider resistor. The readings go into `wiring.toml` first, as R4-R6's
    `measured_ohms`. Then the ratio goes into `POWER_VIN_DIVIDER_PPM` (power check 4, record M2).
  - Only R4's microamp tap uses the VBUS header pin's strip.
- **The battery path is leads and joints**, never strips and never solder (record P3):
  - The pack's own plug goes into the pack-mating half of a cut #1131, red to CELL+ and black to STAR.
  - Solid 22 AWG runs from CELL+ to the INA228's X1.3 (VIN+) screw terminal, and from X1.1 (VIN-) to BATT.
  - The board-mating half of the same #1131 runs from BATT and STAR into the charger's BATT socket.
  - The pack never plugs into the charger's BATT socket while the INA228 meters the battery.
  - OUT leaves by the charger's SYSOUT socket into the OUT joint. That joint takes the 100 Ω load (its
    return to STAR), the INA228's VBUS sense lead and the regulator's input (record P6).
  - The spans keep to record P8's limits (power check 7, the build sheet's power-path table).
  - The charger input is a floating wall adapter on the breakout's own USB-C (record D2).
- **Ground** meets at the STAR joint at pack negative. L_TIE runs from STAR into the regulator GND strip,
  and it's the only conductor between the power and logic grounds (record P4). The NUCLEO's mode-B return
  has its own lead from CN6.7 (record N4).
- **The gauge senses CELL+**, the cell side of the shunt. The board-mating half of a cut #1131 goes in its
  BAT1 socket. Its red lead goes to CELL+ position 3, and its black lead is insulated and folded back. Its
  ground comes over STEMMA QT (record P4, P5).
- **The INA228's VBUS** comes over its own sense lead L_VBUS from X1.2 to the OUT joint (`load_mv`).
  SJ1, its back VBUS-to-VIN+ jumper, stays open (pre-run checklist row C1, power checks 1 and 9).
- **THERM** carries the 10 kΩ NTC (#372, B = 3950), off the breadboard and taped to the pack, on its own
  leads. First you cut the breakout's THERM jumper, R10, to remove its fixed 10 kΩ TS
  resistor (power check 5). The NTC's return goes to the board-B logic ground rail, not STAR (record D2).
  It sets a charge window of about +3.5 to +47 °C.
- **TMR** connects to GND on #4755 (Adafruit's schematic). That disables the safety timers, so there's no
  RTMR (record P9). If TMR floats on the board in hand, write that down and start the charge at 3.85 V or
  more (power check 10).
- **CHG and PGOOD** keep the internal pull-ups while their high level stays at or below VDD + 0.3 V
  (record N4, 2.9 V measured on 2026-10-28/29). Their LEDs' anodes are on OUT (schematic), so a released
  pin sits near OUT - Vf. Power check 6 re-measures it at each step.
- **R_ISET**: the closed 1A jumper selects R9 = 1 kΩ on the schematic (about 0.89 A).
  `power_config.h` holds `POWER_R_ISET_OHM 1000` (R9 on Adafruit's schematic). Power check 2 measures it
  on the board in hand. There's no recorded reading yet.

## History

**2026-10-28/29, as run (record D1, a deviation from the sheet of the day).** The bench ran with the
pack plugged straight into the charger's BATT socket, the LIPO node. That bypassed the INA228 shunt, so
`ishunt` and the charge counters of those runs are invalid.

The gauge sensed OUT until 14:50:08 on 2026-10-28 and the LIPO column from then on. So vcell_v, soc_pct and rate_pct_h before 14:50:08 describe
OUT, not the cell. The INA228's VBUS was on OUT.

We kept the runs as evidence, with `ishunt` and the
charge counters marked invalid by time window. We won't repeat them (step 1's exit needs new runs). The
sheet of that day is `source/baseline-2026-10-29.json`, the first baseline of the build sheet's changes
section. These deviations live here, not in that baseline.

## Parts still to get

The step 1 list is the build-progression record's section 5, "Buy now (step 1)". Compared with that list:

- No meter to buy: we already own the Fluke 87V (record 7.1 Q2).
- No screw-terminal RJ11 breakout: we use the BOB-14021s directly, prepared as above (record 7.1 Q6).
- No RTMR: TMR connects to GND (record P9).
- No soldered pigtails: the #1131 halves go into the WAGO joints stripped and twisted (record P7).

You don't need a second BOB-14021. One product is a panel of two boards (SparkFun's design files),
one for the wind cable and one for the rain cable.

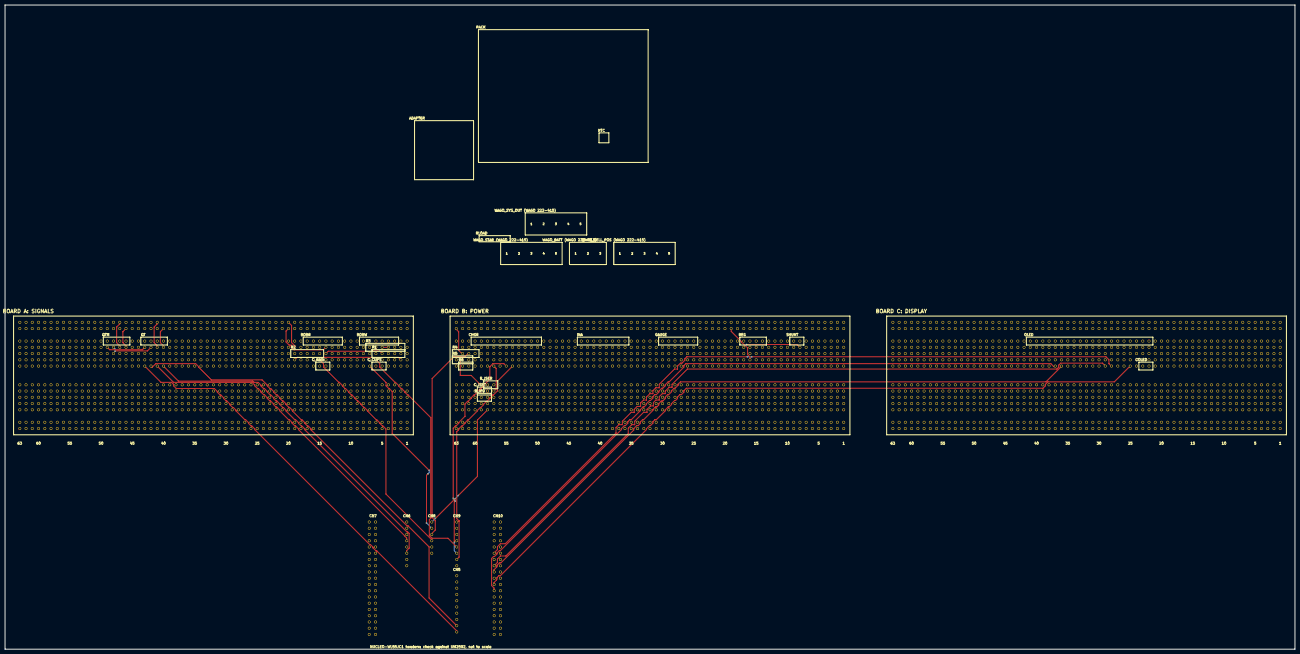
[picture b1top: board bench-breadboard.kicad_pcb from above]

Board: 2 copper layers, 524.4 x 261.9 mm, 4 parts (0 on the bottom side), 32 nets.

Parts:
BB_A: BB_A
BB_B: BB_B
BB_C: BB_C
NUCLEO: NUCLEO

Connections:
W1: BB_A.L+47, BB_A.b47
W2: BB_A.L+41, BB_A.b41
W3: BB_A.L+20, BB_A.b19
W4: BB_A.d2, BB_A.d19
W5: BB_A.L-46, BB_A.b46
W6: BB_A.L-40, BB_A.b40
W7: BB_A.L-20, BB_A.b14
W8: BB_A.c5, BB_A.c14
W9: BB_A.b4, BB_A.b5
W10: BB_A.b43, BB_A.b49
W11: BB_A.b42, BB_A.b48
W12: BB_B.L-63, BB_B.c62
W13: BB_B.d62, BB_B.f59
W14: BB_B.L-19, BB_B.d16
W15: BB_B.e57, BB_B.g57
W16: BB_B.b8, BB_B.b17
W17: BB_A.e41, NUCLEO.CN6.4
W18: BB_B.e54, NUCLEO.CN9.7
W19: BB_A.d6, NUCLEO.CN9.5
W20: BB_A.e40, NUCLEO.CN6.6
W21: BB_A.e43, NUCLEO.CN5.10
W22: BB_A.e42, NUCLEO.CN5.9
W23: BB_B.j58, NUCLEO.CN8.1
W24: BB_C.e36, NUCLEO.CN10.17
W25: BB_C.e25, NUCLEO.CN10.21
W26: BB_C.e29, NUCLEO.CN10.15
W27: BB_C.e37, NUCLEO.CN10.23
W28: BB_C.e28, NUCLEO.CN10.11
W29: BB_B.e55, NUCLEO.CN9.6
W30: BB_A.d15, NUCLEO.CN8.4
W31: BB_A.e7, NUCLEO.CN8.2
W32: BB_B.c61, NUCLEO.CN8.3

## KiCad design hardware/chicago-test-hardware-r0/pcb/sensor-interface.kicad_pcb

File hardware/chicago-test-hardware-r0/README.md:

# Chicago weather-station test hardware R0

Open **index.html** for the illustrated build/order guide and bench equipment list.

## Send to manufacturers

- PCB fabrication: `manufacturing/sensor-interface-gerbers.zip` — five 50 x 35 mm, two-layer, 1.6 mm FR-4 boards.
- Through-hole assembly: also send `manufacturing/BOM.csv`, `manufacturing/placement.csv`, `manufacturing/assembly-top.svg` and `docs/build-and-order.md`.
- 3D printer: `mechanical/nucleo-fit-coupon.stl` first. After fit confirmation, two `nucleo-open-cradle.stl`, one `sensor-interface-base.stl` and one `sensor-ventilated-tray.stl`.
- All fixture STEP files are editable solid geometry. `sensor-interface-bare-pcb.step` is a dimensional reference only, not a printable functional PCB.

## Editable sources

Open `pcb/sensor-interface.kicad_pro` in KiCad 7 or later; schematic, PCB and local symbol/footprint libraries are included. The passive board has no firmware. Scripted regeneration used KiCad 7.0.11 and CadQuery 2.7.0; use `source/build_schematic.py`, `source/build_pcb.py`, `source/build_mechanical.py`, then `source/export_fabrication.sh`. Run the pcbnew scripts with the Python environment supplied by your KiCad installation. The CAD generator is fully editable parametric Python; STEP also opens in FreeCAD/Fusion/other CAD tools.

Verification scripts: `source/verify_electrical.py` and `source/check_meshes.py`. Validation outputs are included. Physical fit and electrical bench qualification remain untested. No manufacturer order has been placed.

The bundle is an engineering prototype: a passive sensor connection/current-test board plus open bench fixtures around purchased Nucleo and SHT45 modules. It does not contain the later battery/solar/controller PCB or a weatherproof enclosure. The Stage-0 software starter remains a separate package.

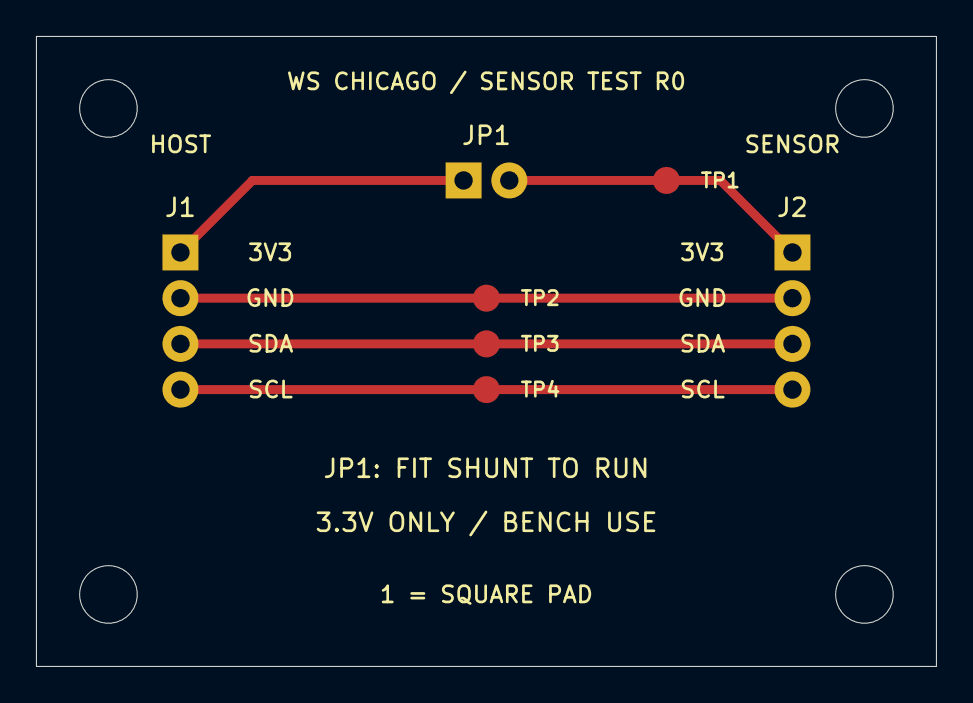
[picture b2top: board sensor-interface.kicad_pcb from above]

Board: 2 copper layers, 50.0 x 35.0 mm, 11 parts (0 on the bottom side), 5 nets.

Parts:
H1, H2, H3, H4: M3_NPTH; MountingHole_3.2mm
J1, J2: TSW-104-07-G-S; Header_1x04_VerticalRow
JP1: TSW-102-07-G-S; Header_1x02_HorizontalRow
TP1: 3V3_SENSOR; TestPad_1.5mm
TP2: GND; TestPad_1.5mm
TP3: SDA; TestPad_1.5mm
TP4: SCL; TestPad_1.5mm

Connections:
3V3_IN: J1.1, JP1.1
3V3_SENSOR: J2.1, JP1.2, TP1.1
GND: J1.2, J2.2, TP2.1
SCL: J1.4, J2.4, TP4.1
SDA: J1.3, J2.3, TP3.1

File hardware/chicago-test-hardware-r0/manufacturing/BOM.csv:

Reference,Quantity_per_board,Manufacturer,MPN,Description,Mounting,Notes
"J1 J2",2,Samtec,TSW-104-07-G-S,"4-pin 2.54 mm vertical male header",Through-hole,"Top side; 1.02 mm finished holes; pin 1 square"
JP1,1,Samtec,TSW-102-07-G-S,"2-pin 2.54 mm vertical male header",Through-hole,"Top side; row runs horizontally on PCB"
JP1_shunt,1,Samtec,SNT-100-BK-G,"2.54 mm removable shorting shunt",Manual fit,"Fit over JP1 after soldering and electrical inspection; not in placement.csv"
